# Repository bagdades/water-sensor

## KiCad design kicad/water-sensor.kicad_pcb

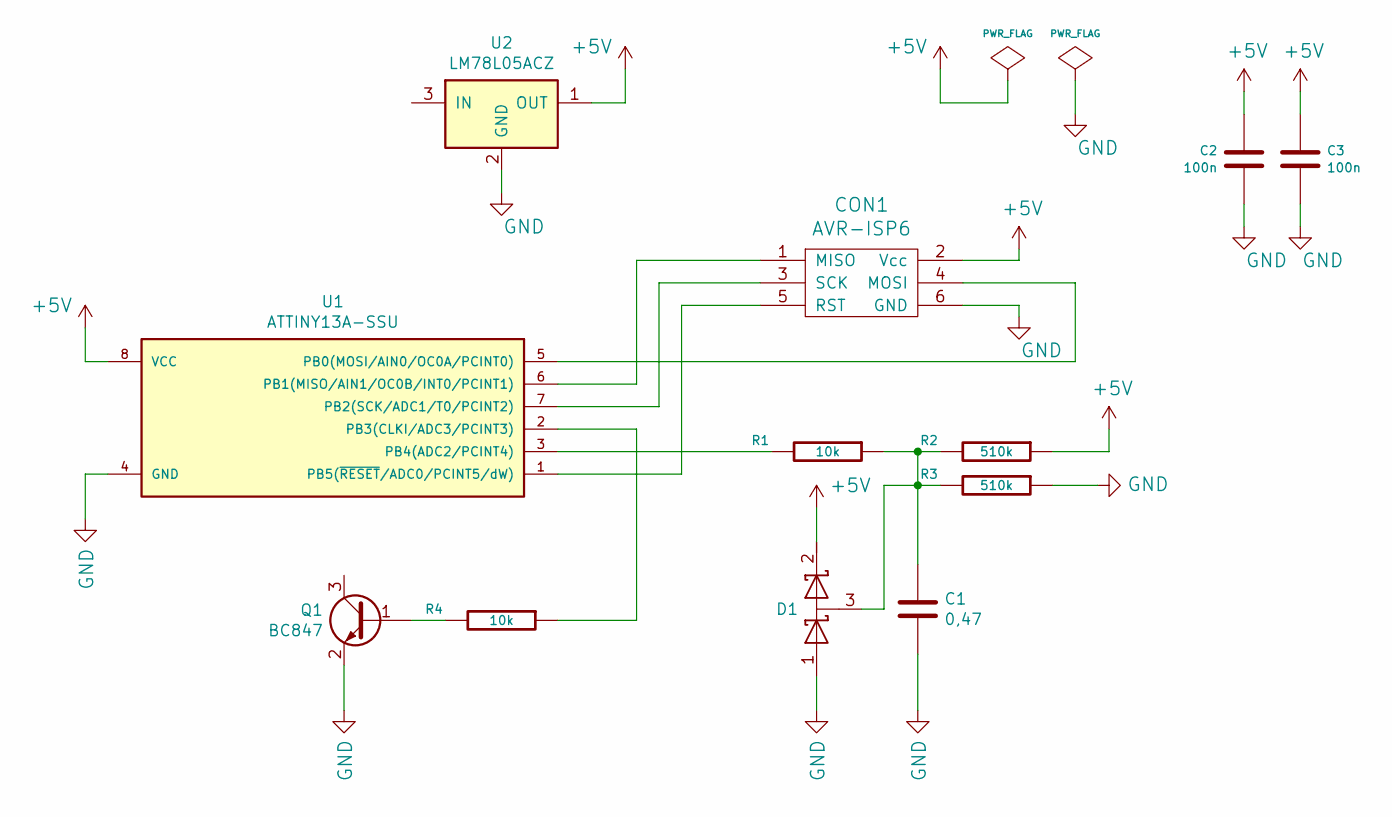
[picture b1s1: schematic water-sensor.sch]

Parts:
C1: 0,47; C_0805
C2, C3: 100n; C_0805
CON1: AVR-ISP6; pin_strip_3x2
D1: D_Schottky_x2_Serial_AKC
Q1: BC847; SOT-23
R1, R4: 10k; R_0805
R2, R3: 510k; R_0805
U1: ATTINY13A-SSU; SOIC-8_3.9x4.9mm_Pitch1.27mm
U2: LM78L05ACZ; TO-92_Molded_Narrow

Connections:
+5V: C2.1, C3.1, CON1.2 (Vcc), D1.2 (K), R2.1, U1.8 (VCC), U2.1 (OUT)
GND: C1.2, C2.2, C3.2, CON1.6 (GND), D1.1 (A), Q1.2 (E), R3.1, U1.4 (GND), U2.2 (GND)
unnamed: C1.1, D1.3 (common), R1.1, R2.2, R3.2
unnamed: CON1.1 (MISO), U1.6 (PB1(MISO/AIN1/OC0B/INT0/PCINT1))
unnamed: CON1.3 (SCK), U1.7 (PB2(SCK/ADC1/T0/PCINT2))
unnamed: CON1.4 (MOSI), U1.5 (PB0(MOSI/AIN0/OC0A/PCINT0))
unnamed: CON1.5 (RST), U1.1 (PB5(~RESET~/ADC0/PCINT5/dW))
unnamed: Q1.1 (B), R4.2
unnamed: R1.2, U1.3 (PB4(ADC2/PCINT4))
unnamed: R4.1, U1.2 (PB3(CLKI/ADC3/PCINT3))

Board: 2 copper layers, 11 parts (0 on the bottom side), 10 nets, no tracks yet.

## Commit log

2017-03-13 Start
2017-03-13 Create source
2017-03-13 Add source
2017-03-13 End work_13.03
2017-03-18 Work
2017-03-18 End work 1803
